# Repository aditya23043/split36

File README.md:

# 36 Key Split Ergonomic Keyboard

## Block Diagram

## BOM

| Item                                                           | Qty | Total Price | Ordered From |
| -------------------------------------------------------------- | --- | ----------- | ------------ |
| PCB                                                            | 2   | ₹ 800       | Robu.in      |
| 3D printed Cases (optional but recommended)                    | 2   | ₹ 652       | Robu.in      |
| Akko V3 Creamy Yellow Pro Mechanical Switch                    | 45  | ₹ 999       | StacksKB.com |
| 3.5mm TRRS Jack                                                | 2   | ₹ 28        | Robu.in      |
| Raspberry Pi Pico                                              | 2   | ₹ 700       | Robu.in      |
| Header 1x40 pin                                                | 2   | ₹ 14.6      | Robu.in      |
| High Quality Ultra Flexible 30AWG Silicone Wire - Black        | 5   | ₹ 25.00     | Robu.in      |
| M2 X 6mm Brass Threaded Inserts (Dia. 2mm, Length 6mm)         | 12  | ₹ 26.40     | OnlyScrew.in |
| M2 X 6mm Phillips Pan head SS 304 Screw (Dia. 2mm, Length 6mm) | 12  | ₹ 24.00     | OnlyScrew.in |
| Total                                                          | -   | ₹ 3269      |              |

## Order

<details>
<summary>All the stuff ordered in regards to this project</summary>

> This is not the actual concise BOM\
> All this is just the stuff I ordered related to this project

- StacksKB.com

  - Akko V3 Creamy Yellow Pro Switch (Pack of 45) × 1
  - Order Number: 30456
  - Cost: 899 + 100 (delivery) = ₹ 1000
  - Order Date: 2025-02-08

- Robu.in

| Item              | Qty | Cost  |
| ----------------- | --- | ----- |
| TRRS Jack         | 2   | ₹ 28  |
| Raspberry Pi Pico | 1   | ₹ 349 |
| Header 1x40 pin   | 12  | ₹ 88  |
| Ball Bearing      | 2   | ₹ 38  |
| Handling charges  | -   | ₹ 25  |
| TOTAL             | -   | ₹ 528 |

- Robu.in (2nd)

| Item                                                                | Qty | Cost                          |
| ------------------------------------------------------------------- | --- | ----------------------------- |
| USB 3.1 Female Socket Type C Connector 24 Pins Breakout PCB Board   | 2   | ₹ 98.00                       |
| Wire Stripper Flat Nose Cable Cutter with Practical Punch Down Tool | 1   | ₹ 18.00                       |
| High Quality Ultra Flexible 30AWG Silicone Wire - Black             | 5   | ₹ 25.00                       |
| UL1007 26AWG PVC Electronic Wire - Black                            | 2   | ₹ 14.00                       |
| High Quality Ultra Flexible 22AWG Silicone Wire - Black             | 2   | ₹ 36.00                       |
| Heat Shrink Sleeve 1mm Red Industrial Grade WOER (HST)              | 4   | ₹ 20.00                       |
| Piezo Buzzer 35mm                                                   | 1   | ₹ 16.00                       |
| Subtotal:                                                           | -   | ₹ 227.00                      |
| Shipping:                                                           | -   | ₹ 49.00 via STANDARD SHIPPING |
| Cash Handling Charges:                                              | -   | ₹ 25.00                       |
| Total:                                                              | -   | ₹ 301.00                      |

- OnlyScrew.in

| Item                                                                   | Qty | Cost     |
| ---------------------------------------------------------------------- | --- | -------- |
| M2 X 6mm Brass Threaded Inserts (Dia. 2mm, Length 6mm)                 | 12  | ₹ 26.40  |
| M2 X 4mm Phillips Pan head SS 304 Screw (Dia. 2mm, Length 4mm)         | 12  | ₹ 21.60  |
| M2 X 3mm Brass Threaded Inserts (Dia. 2mm, Length 3mm)                 | 12  | ₹ 19.20  |
| M2 X 6mm Phillips Pan head SS 304 Screw (Dia. 2mm, Length 6mm)         | 12  | ₹ 24.00  |
| M2 Hex Nut SS304 (Dia. 2mm)                                            | 12  | ₹ 19.20  |
| M3 X 12mm Phillips CSK SS 304 Screw (Dia. 3mm, Length 12mm)            | 10  | ₹ 16.00  |
| Allen Key 2mm Chromium Vanadium Steel                                  | 1   | ₹ 6.20   |
| M3 X 12mm Hex (Allen) Button Head SS 304 Screw (Dia. 3mm, Length 12mm) | 8   | ₹ 17.60  |
| Subtotal                                                               | -   | ₹ 150.20 |
| Shipping                                                               | -   | ₹ 99.00  |
| Taxes                                                                  | -   | ₹ 27.04  |
| Total                                                                  | -   | ₹ 276.24 |

</details>

## Case Designing

- I am aiming for a sandwich case which consists of a bottom part, middle part for padding, another plate in which pcb is resting and the top switch mount plate
- The bottom plate will be of 3mm ABS (non metal laser cut) so that the keyboard has a solid base
- The next plate is the middle one but it is a little bit smaller in inner part so that the PCB can rest on top of it
  - this plate's height will be -> 3mm because we need at least (3.3-1.6) = 1.7mm clearance and having another 1.3mm would be nice so that the soldered wires can go through
  - note: 3.3mm is the distance between the bottom-most point of the MX switch and the point which rests on the PCB
  - and the height of the PCB is 1.6mm
- Next is the other bottom plate with the pcb cutout in the middle so that the pcb can be put into it and also provides the gap between the previous middle layer and the switch mount plate
  - This will be of height -> (5-1.5)+(1.6) = 5.1mm
- Lastly, we have the switch mount plate which obviously holds the MX switches and needs to be 1.5mm in height

## Materials Used for the case (complex case)

| Plate     | Material              | Cost |
| --------- | --------------------- | ---- |
| Bottom    | Laser cut Acrylic 3mm |
| Middle    | Laser cut Acrylic 3mm |
| Middle v2 | Laser cut Acrylic 5mm |
| Top       | ABS FDM 3d printed    |

> As of now (025-02-19 23:20), I am pausing this sandwich case idea and shifting to just a single case which encloses the PCB from the bottom and sides\
> I would have preferred to have a switch mount plate as well because it adds stability and reduces dust residue in the keyboard but I would like to get started with a simpler case than the sandwich one and also, I would like to use the existing mounting stuff I have bought i.e. the m2x3mm brass inserts and hence I am heading for this approach

## Simple Case

- This case was costing me about Rs. 389 on https://robu.in with ABS and 15% infill
- I believe that is a bit high for me since this is just half of the keyboard
- So, I reduced the cost down to about Rs. 300 by putting the PCB a bit lower and instead of the 5mm solid base, we now have a 2mm solid base which makes a little bit less solid but its not a huge problem
- This is the case with the PCB after the cost cut

- Order placed for this case for Rs.335 along with the mount plate for this project -> https://github.com/aditya23043/Tekken_Controller
- Totalling: Rs. 463 (335 + 79 (mount plate) + 49 (delivery))

## 2025-02-26 23:54

- The case has arrived for one of the halves since I wanted to make sure there were no issues with my design
- And guess what? Yes, there is a major issue with the design
- I had not taken printing error in mind and hence did not account for tolerance issues
- The PCB just wont go in flush. It seems like if the case was just 0.5-1mm more larger on the inside, the PCB would have rested perfectly
- I have updated the 3D case files in the repo to include a 0.7mm clearance on the inside
- As for the case, I have taken suggestions from seniors and batchmates from the Electroholics Club of IIITD
- They have suggested to either use the thermal property of ABS in order to mould it into a bit bigger enclosure
- Or sand the edges down a bit to accomodate the PCB perfectly
- I will be taking the latter approach since that seems more fail proof in my mind
- And hence, I have ordered this sand paper set from amazon -> [Sand paper](https://www.amazon.in/Abrasive-Automotive-Woodworking-Furniture-Finishing/dp/B0CCW1BG6J?crid=2EEL0M61VZAA&dib=eyJ2IjoiMSJ9.Zoi8ylSky-5luMBW1yZJDoSybKyFAd-nqliej5kaOOlOpCvAWyQ41mtm_BK3hccGk31BMp2cViJyyWQd6a_diGoK0G64POys9TNYCAbUBpH24bBg0yZ7kc0Ak9Pfc_61XdJiMc7flElSorGCEcOXjIZMTRTRceEs2cXiosr3PirVU5lLTFYQC7vD3jknDQvFn2VQ5Xwbg4kThXJXX_U_AD_CbIjYicfF7zHdDg82PSNY9mOjZS1VNdKjRHVu5uBzZ4lRd1IlxIwzcVhsADxnlQQYXiG4B_37tawKm34SAPIcsIGwqtalY5JfByuImBkNebYDzTPX32AZYsfDKeUq7G12zp3VJ4RzMkF1yfA55NbeXZ8WBsbFUSJUn487lN6kKEX7saYSj2JCtrtfa6v1f31TochDW9mhu5mwZfobleQB-t04E13b-aYj9pGOqL9u.koHrfVWDqWvgJBQTqdjGDcFOiomCGaOogGteUhE_4SI&dib_tag=se&keywords=sandpaper%2Bfor%2Bplastic&qid=1740584809&sprefix=sandpaper%2Bfor%2Bplast%2Caps%2C259&sr=8-2&th=1)

## 2025-03-18 23:48

- Instead of trying to make do with the case without tolerances, I have decided to add 1mm tolerance to the current design and order it again
- For ABS 15% infill 2mm default nozel, it is costing me Rs. 277 + Rs. 49 = Rs. 326

## 2025-03-29 00:23

- Added brass heat inserts in order to mount the pcb to the case using M2 screws
- Finished soldering the mechanical switches, header pins for MCU and the TRRS jack onto the PCB.

## 2025-03-31 23:45

- Deep purple keycaps came in today
- Fixed the skew in keyswitches -> https://www.reddit.com/r/ErgoMechKeyboards/comments/1jmeygr/the_switches_on_my_custom_cornelike_keyboard_do/

## 2025-03-05 10:03

- Case for the right half ordered from https://Robu.in
- Firmware for the left half done
  - Also includes the code for "key held down" event
- [x] Right half assembly
- [ ] Right half firmware

## 2025-04-11 23:13

### Major Issue

- The footprint used for the MX switches (from ScottoKeeb's github repo) had label -> MX 1.00u Reversible written on it. However, it means reversible in the sense that we can swap north facing and south facing switches, not for mutli sided switches
- Hence, the assembly of the right half is on hold until the new PCB arrives.
- In the modified kicad project I have used the SW_MX_REVERSIBLE footprint from -> https://github.com/daprice/keyswitches.pretty
- Furthermore, I have added the kicad project in this repo inside the `pcb/` directory
- 2025-04-11 23:26 -> PCB order placed
  - Cost: ₹1935 for 5 PCBs
  - Nearly: ₹400 per PCB

## 2025-05-03 23:13

- Right Half assembly done

## Major Issue 2.0

- The TRRS jack connection on the second half is technically correct but the problem is that since the right half is just the flip of left half PCB, the microcontroller should either be soldered reverse or else the pins are flipped wrt the vertical axis
- Due to this, the connections of the TRRS jack are reversed as well
- Instead of GND, VSYS, GP0, GP1; we have -> GND, GP1, VBUS, VSYS which is very wrong in context of the code logic
- Hence, I had to scratch out all the copper tracks manually connected to the TRRS jack and connect them with the MCU manually using wires with the following connections

```
TRRS
4 3 2
    1

DEFAULT
1 GND
2 GP1
3 VBUS
4 VSYS

WHAT WE WANT
1 GND
2 VSYS
3 GP0 (SDA)
4 GP1 (SCL)
```

- And finally, with testing, I am able to confirm that the right half can now be powered properly with just the left half connected with the system
- So, as of now, this prototype's hardware stuff has been completed
- [X] TODO: Firmware

# Finished the project! 
- Presentation: https://docs.google.com/presentation/d/1XDV15suqviizSQfUHfM2_ha1iqeUGhER_RJtFe0Dyr4/edit?usp=sharing
- LinkedIn Post: https://www.linkedin.com/posts/aditya23043_just-completed-my-most-ambitious-project-activity-7335380768921198593-B5wh?utm_source=share&utm_medium=member_desktop&rcm=ACoAAEb0rpkBcvkxpg6PQ2YDkrWiA3oRIAywLL4

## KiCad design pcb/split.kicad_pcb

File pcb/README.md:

# Important Stuff
- Planning on having m2 screws mounted through the switch mount plate then through the pcb and then inside the brass heat inserts mounted in the bottom case
	- Clearance needed:
		- 5mm : top of switch mount plate to top of pcb
		- 3.3mm : top of pcb to bottom of mx pins
		- 3mm : brass insert
		- TOTAL : 11.3mm (ordering both)

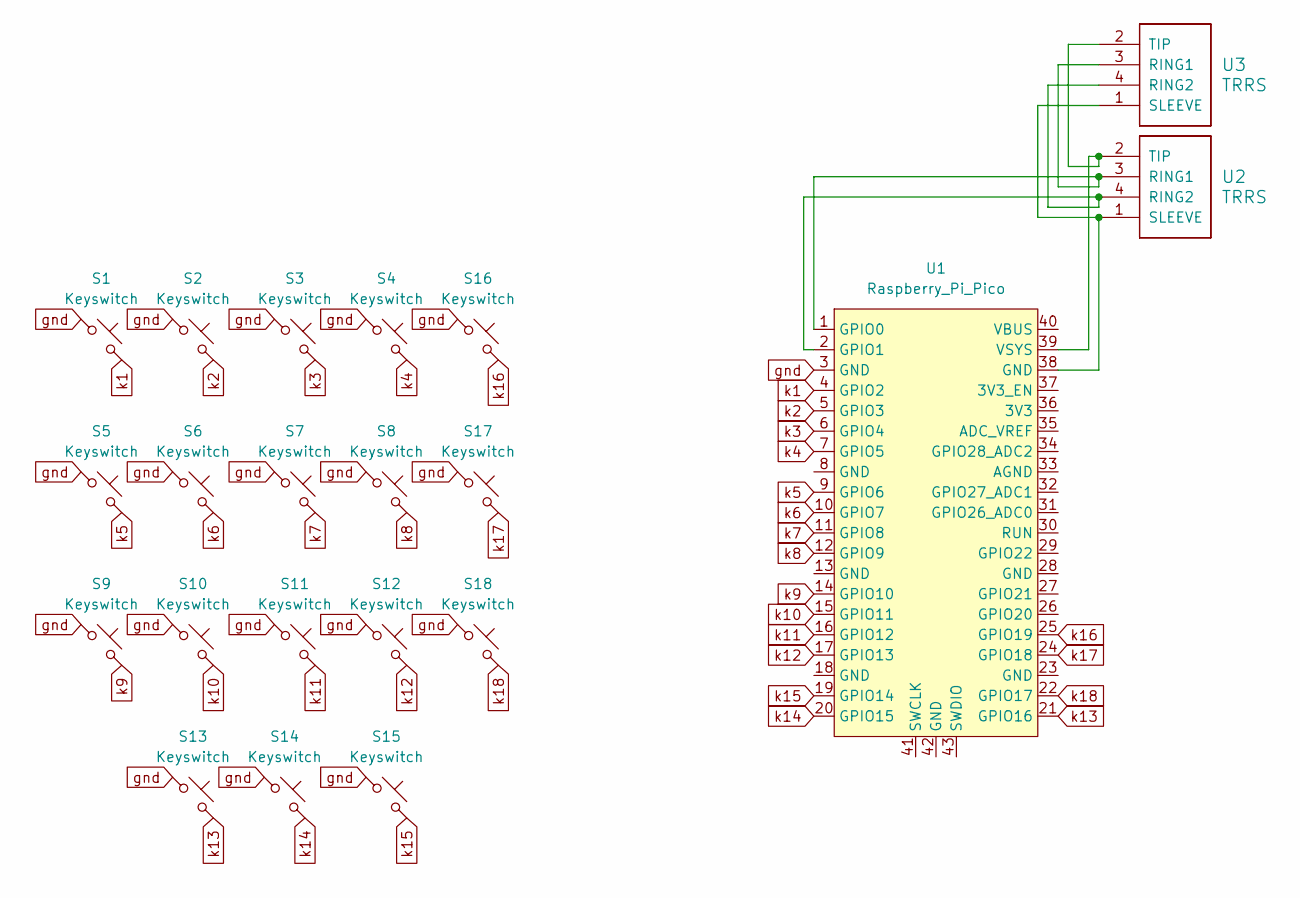
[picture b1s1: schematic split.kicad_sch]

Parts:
S1, S2, S3, S4, S5, S6, S7, S8, S9, S10, S11, S12, S13, S14, S15, S16, S17, S18: Keyswitch; SW_MX_reversible
U1: Raspberry_Pi_Pico
U2, U3: TRRS; TRRS-PJ-320D

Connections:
unnamed: U1.1 (GPIO0), U2.3 (RING1), U3.3 (RING1)
unnamed: U1.2 (GPIO1), U2.4 (RING2), U3.4 (RING2)
unnamed: U1.39 (VSYS), U2.2 (TIP), U3.2 (TIP)
unnamed: U1.38 (GND), U2.1 (SLEEVE), U3.1 (SLEEVE)
gnd: S1.1, S2.1, S3.1, S4.1, S5.1, S6.1, S7.1, S8.1, S9.1, S10.1, S11.1, S12.1, S13.1, S14.1, S15.1, S16.1, S17.1, S18.1, U1.3 (GND)
k1: S1.2, U1.4 (GPIO2)
k2: S2.2, U1.5 (GPIO3)
k3: S3.2, U1.6 (GPIO4)
k4: S4.2, U1.7 (GPIO5)
k5: S5.2, U1.9 (GPIO6)
k6: S6.2, U1.10 (GPIO7)
k7: S7.2, U1.11 (GPIO8)
k8: S8.2, U1.12 (GPIO9)
k9: S9.2, U1.14 (GPIO10)
k10: S10.2, U1.15 (GPIO11)
k11: S11.2, U1.16 (GPIO12)
k12: S12.2, U1.17 (GPIO13)
k13: S13.2, U1.21 (GPIO16)
k14: S14.2, U1.20 (GPIO15)
k15: S15.2, U1.19 (GPIO14)
k16: S16.2, U1.25 (GPIO19)
k17: S17.2, U1.24 (GPIO18)
k18: S18.2, U1.22 (GPIO17)

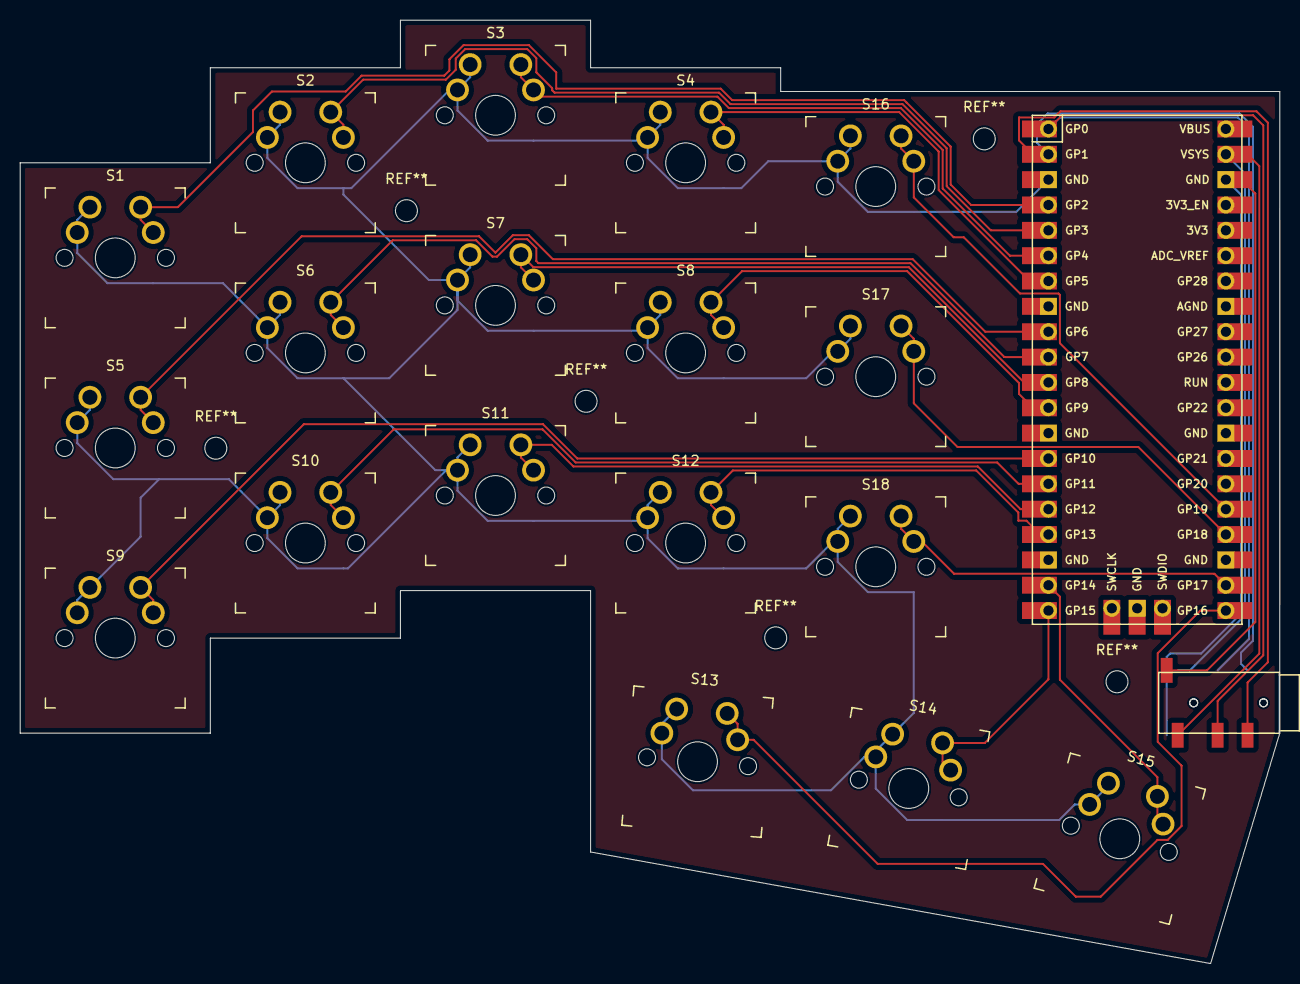
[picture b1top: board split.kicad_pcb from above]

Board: 2 copper layers, 126.2 x 94.5 mm, 21 parts (1 on the bottom side), 23 nets.

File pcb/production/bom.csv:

Designator,Footprint,Quantity,Value,LCSC Part #
"S1, S10, S11, S12, S13, S14, S15, S16, S17, S18, S2, S3, S4, S5, S6, S7, S8, S9",SW_MX_reversible,18,Keyswitch,
U1,Raspberry_Pi_Pico,1,Raspberry_Pi_Pico,
"U2, U3",TRRS-PJ-320D,2,TRRS,

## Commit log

2025-02-07 order placed
2025-02-13 bom updated
2025-02-14 readme updated
2025-02-19 major advancements in case building
2025-02-19 moved the 'all items' stuff to a collapsable fold
2025-02-19 switched mx dimension images
2025-02-19 trying to make imgs work
2025-02-19 hopefully final commit regarding mx dimension image
2025-02-19 offical mx switch dimension image found
2025-02-19 simple case almost done
2025-02-19 done with the simple case
2025-02-19 readme updated to include the simple case photos
2025-02-21 pushed the cheaper single case
2025-02-21 order placed for the case
2025-02-26 simple case received but tolerance issue
2025-03-25 reordered case with padding
2025-03-25 added BOM
2025-03-25 added block diagrtam
2025-03-25 updated BOM
2025-03-28 assembling done
2025-03-31 purple keycaps and source code pushed
2025-04-08 dev log updated for 3rd april
2025-04-11 resolving a hurdle
2025-05-03 added photo
2025-05-05 firmware finally done
2025-05-06 keymap pushed
2025-05-06 minor updates
2025-06-24 added link for presentation and linkedin
2025-07-07 qmk config finally donw
